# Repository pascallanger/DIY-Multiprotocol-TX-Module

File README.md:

# Multiprotocol TX Module

The **Multiprotocol Tx Module** (or **MULTI-Module**) is a 2.4GHz transmitter module which enables almost any transmitter to control many different receivers and models, including many popular helicopters, planes, quadcopters, and miniquads.

The main forum for protocol requests and questions is on [RCGroups.com](https://www.rcgroups.com/forums/showthread.php?2165676-DIY-Multiprotocol-TX-Module/page10000).

If you like this project and want to support further development please consider making a [donation](docs/Donations.md).  

<table cellspacing=0>
  <tr>
    <td align=center width=200><br><b>€5</b></td>
    <td align=center width=200><br><b>€10</b></td>
    <td align=center width=200><br><b>€15</b></td>
    <td align=center width=200><br><b>€25</b></td>
    <td align=center width=200><br><b>Other</b></td>
  </tr>
</table>

## Development status

Multiprotocol downloads: 

Current Multiprotocol code check status: . Download the latest **test** build [here](https://downloads.multi-module.org/latest-test/).

Current Multiprotocol boards check status: 

## Quicklinks
* [Download latest releases of the firmware](https://github.com/pascallanger/DIY-Multiprotocol-TX-Module/releases) and [instructions to upload .hex files](docs/Advanced_Manually_Setting_ATmega328_Fuses.md)
* [Forum on rcgroups](http://www.rcgroups.com/forums/showthread.php?t=2165676)
* [Available Protocols list](Protocols_Details.md)
* [The old documentation](docs/README-old.md)

## Outline of the documentation
1. Introduction (this page)
1. [Available protocols](Protocols_Details.md)
1. [Transmitters and serial/telemetry options](docs/Transmitters.md)
1. [Module Hardware options](docs/Hardware.md)
1. Compiling and programming the module
    * [Atmega328p Multiprotocol Module](docs/Compiling.md)
    * [STM32 Multiprotocol Module](docs/Compiling_STM32.md)
    * [OrangeRX Module](docs/Compiling_OrangeTx.md)
1. [Transmitter Setup](docs/Transmitters.md) 
    * [Channel Order](docs/Channel_Order.md)
1. [How to for popular models](docs/Models.md)
1. [Troubleshooting](docs/Troubleshooting.md)
2. [Advanced Topics (not for the fainthearted!)](docs/Advanced_Topics.md)

## Introduction
A functioning MULTI-Module consists of (see image below):  

1.  A host RC Tx

1. A Multiprotocol Transmitter Module (MULTI-Module) that connects to a host transmitter.  This module is typically comprised of
   * A microcontroller (currently ATMega328P or STM32) that interfaces with the Tx, controls the module functions and forwards the RC commands to the RF hardware
   * One or more (but at least one) RF modules that provide the capability to communicate with RC receivers.  To communicate with the receiver the RF module in the Tx must match with the RF module type in the receiver.  The four most common 2.4GHz RF chips on the market are supported TI CC2500, Nordic NRF24L01, Cypress CYRF6936, and the Amiccom A7105
   * MULTI-firmware loaded on to the microprocessor.  At a high level, this firmware performs a few different functions: 
     * It interfaces with signals from the host Tx and decodes these for transmission to the model, it manages the activation of the correct hardware RF module for each protocol
     * It implements the unique communication protocols for each receiver/model and manages the all-important binding process with a receiver/model
     * In the case of some protocols (for example DSMX and FrSky) it receives and decodes the telemetry information and makes this available to the radio.
1. The physical 2.4GHz antenna (or in some cases multiple antennas) for the modules

One of the most attractive features of the MULTI-module is the ability to send telemetry signals back to the transmitter. The MULTI-Module is fully telemetry capable for all protocols that support telemetry.  Your ability to use the telemetry information depends on  your radio hardware and firmware.

In constructing a functioning MULTI-Module there are important choices to be made and tradeoffs to be aware of.  The most important are:

## **Choice 1:** Which MULTI-Module hardware option 

There are currently four generic paths to get your hands on an MULTI-Module.  These are outlined in detail on the [hardware](docs/Hardware.md) page.  Here they are, in order of increasing difficulty:
  - **Ready-made MULTI-Module** - Available from Banggood which includes a 4-in-1 RF module and an antenna switcher
  - **DIY MULTI-Module** - Purchase one of the PCB options from [OSHPark](http://www.oshpark.com) and then solder on your own components and RF modules (the two options differ in the MCU used - either an ATmega328P or a STM32F1)
  - **OrangeRx MULTI-Module** You can turn the OrangeRx DSM2/X Tx module (available from HobbyKing) into a MULTI-Module to increase the number of supported protocols, add telemetry as an option and bind more successfully with problematic bind-and-fly models. 
  - **Scratchbuild a MULTI-Module** -  Build the module from scratch using perfboard base, an Arduino Pro Mini and discrete components.

The last option is where it all started and how the pioneers in this project made their boards.  However, due to the growing interest in “one module to rule them all” you now have options to purchase a ready-made board (with old firmware that you will need to upgrade).  

For more information on these options see the [hardware](docs/Hardware.md) page

## **Choice 2:** Which RF modules to include in the MULTI-Module

This depends on your specific needs.  However, recent the availability of the 4-in-1 RF modules from Banggood for less than $35 makes it easy to “have it all”.  Most manufacturers of RC systems (Spektrum, FrSky, FlySky) and toys (Syma, Hubsan, etc.) use one of these four RF chips to manage the RF link between the transmitter and the reciever/model.  Here is an incomplete list of the RF modules and some of the most popular toys that use them.  For the complete list see the [Protocol Details](Protocols_Details.md) page.

|Manufacturer|RF Chip|Example Protocols|
|---|---|---|
|Cyprus Semiconductor|CYRF6936|DSM/DSMX|
|||Walkera Devo|
|||J6Pro|
|Texas Instruments|CC2500|FrSky|
|||Futaba SFHSS|
|Amiccom|A7105|FlySky|
|||FlySky AFHDS2A|
|||Hubsan|
|Nordic Semiconductor|NRF24L01|HiSky|
|||Syma|
|||ASSAN|
|||and most other Chinese models|

For example, if you have no interest in binding your Tx to an model with and FrSky or Futaba SFHSS receiver you do not need to include the CC2500 RF module in your system.

## **Choice 3:** Which protocols to upload to the MULTI-Module

As the list of supported protocols grows even the STM32 ARM microcontroller cannot hold all of the protocols. You can select the protocols you need and complie your own firmware. Fortunately, the process of selecting and compiling is not too difficult and it is fully documented on the [Compiling and Programming](docs/Compiling.md) page. You can also download firmware from the [Multi-Module](https://downloads.multi-module.org) website. These firmware files have been split into two groups, surface "SFC" and air "AIR". You can check which protocols are included in each of these groups in the [Validate.h](Multiprotocol/Validate.h) source file.

In the case of the ATmega328, the memory required by all the possible protocols exceeds the 32KB flash limit considerably. This means that you will need to make a choice of which protocols you will compile into your firmware.

## **Choice 4:** Choosing the type of interface between the MULTI-Module and your radio (PPM or Serial)

The MULTI-Module supports industry standard PPM interface that works with all transmitters with either:  
 - a module bay or
 - a trainer port or
 - any PPM signal that can be accessed inside the Tx.

Most of the older FM radios support the PPM interface.

If you are the owner of a transmitter that supports the er9X/erSky9X or OpenTX firmwares (Frsky Taranis, Horus or the FlySky TH9X or the Turnigy 9X family) you have the additional option to use a serial protocol to communicate between your Tx and the MULTI-Module. (Owners of Walkera Devo transmitters should look at the [Deviation Tx](http://www.deviationtx.com) project for how to achieve the same end goal). This serial protocol does not require any hardware modifications, but will likely require updating the firmware on your radio. For those willing to do this, there are some nice advantages:
  - The model protocol selection, associated parameters, failsafe and binding is done from the Model Settings menu on the Tx
  - For telemetry capable transmitters, the telemetry integration is done seamlessly with the Tx firmware. (Note that FrSky TH9X/Turnigy 9X/R transmitters require a telemetry mod to be done before telemetry can work).  Click on the link corresponding to your Tx on the [Transmitters](docs/Transmitters.md) page for more details.

# How to get started?
1. Browse the [Protocols](Protocols_Details.md) page to see which protocols you would like on your module
1. Go to the [Hardware Options](docs/Hardware.md) page to decide which of the MULTI-Module hardware options appeals to you and which RF modules you plan to integrate
1. Once you have your module, you should review what jumper settings or modifications are required to the module to support serial communication and possibly telemetry
1. Go to [Compiling and Programming](docs/Compiling.md) page to download, compile and program your MULTI-Module
1. Finally, you should visit the setup page for your transmitter by clicking on the link corresponding to your Tx on the [Transmitters](docs/Transmitters.md) page to configure the last few settings before you can fly to your heart’s content!!!!!

# Troubleshooting
Visit the [Troubleshooting](docs/Troubleshooting.md) page.  Please bear in mind that the MULTI-Module is a complex system of hardware and software and it may take some patience to get it up and running.  Also remember that the developers of the system are actual users of the system.  This means that at any moment in time the system is working perfectly for them.  A corollary to this is that if you are struggling there are likely two scenarios.  First, that the problem is with your hardware or with your configuration, second, and much more unlikely but not impossible scenario, is that you are struggling with a new undiscovered bug.  (The author of this documentation speaks from experience ;-)   Please check the RC Groups forum and search for keywords relating to your problem before posting a reply.  When you do post a reply please so humbly and respectfully – you will find many helpful people there.  In your reply please include as much relevant information as possible and attach compilation output and ```_Config.h``` files as text attachments to keep the forum clean.
# A final word
A very big thanks to all the people who have shared their time so graciously to create this great project.  If you come across them on RC Groups, please be kind and show appreciation.  In no particular order:
* Pascal Langer (rcgroups: hpnuts)
* Ben Lye (rcgroups: benzo99)
* Midelic (rcgroups: midelic)
* Mike Blandford (rcgroups: Mike Blandford)
* schwabe - from OpenTX 
* PhracturedBlue – from [Deviation TX project](http://www.deviationtx.com)
* goebish – from [Deviation TX project](http://www.deviationtx.com)
* victzh – from [Deviation TX project](http://www.deviationtx.com)
* hexfet – from [Deviation TX project](http://www.deviationtx.com)

Your help would be greatly appreciated.  If protocol reverse-engineering and dev is not your thing then any help with testing and contributing to the documentation would be amazing.  Given the number of different Tx/module hardware/RF module/protocol/model combinations the process of testing and documenting is a major bottleneck for the developers.  Anything you can do to help will free them up to do even greater things. 

If you like this project and want to support further development please consider making a [donation](docs/Donations.md).

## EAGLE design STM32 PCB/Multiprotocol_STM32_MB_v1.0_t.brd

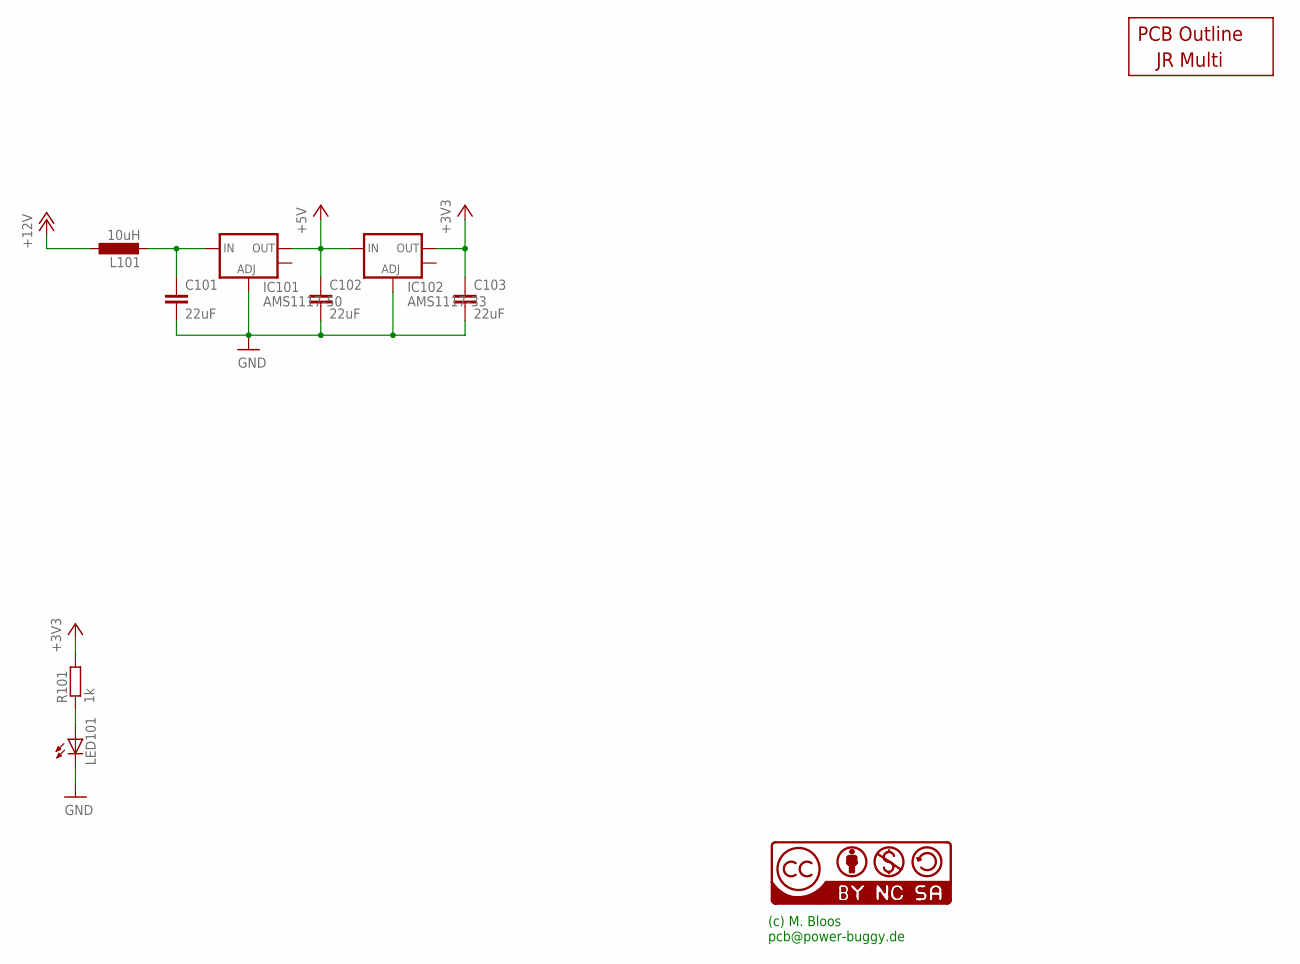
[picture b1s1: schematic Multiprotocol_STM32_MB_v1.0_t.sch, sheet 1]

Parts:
C101, C102, C103: 22uF; C1210K
IC101: AMS1117-50; SOT223
IC102: AMS1117-33; SOT223
L101: 10uH; L1812
LED101: LED3MM
NIX101: CC-NC-BCNIX; CC-NC-B_NIX
OUTLINE101: JR_MULTI
R101: 1k; R0805

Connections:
+3V3: C103.1, IC102.2 (OUT), R101.2; also elsewhere on the board
+5V: C102.1, IC101.2 (OUT), IC102.3 (IN); also elsewhere on the board
+12V: L101.1; also elsewhere on the board
GND: C101.2, C102.2, C103.2, IC101.1 (ADJ), IC102.1 (ADJ), LED101.K (C); also elsewhere on the board
unnamed: C101.1, IC101.3 (IN), L101.2
unnamed: LED101.A, R101.1

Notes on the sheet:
(c) M. Bloos pcb@power-buggy.de

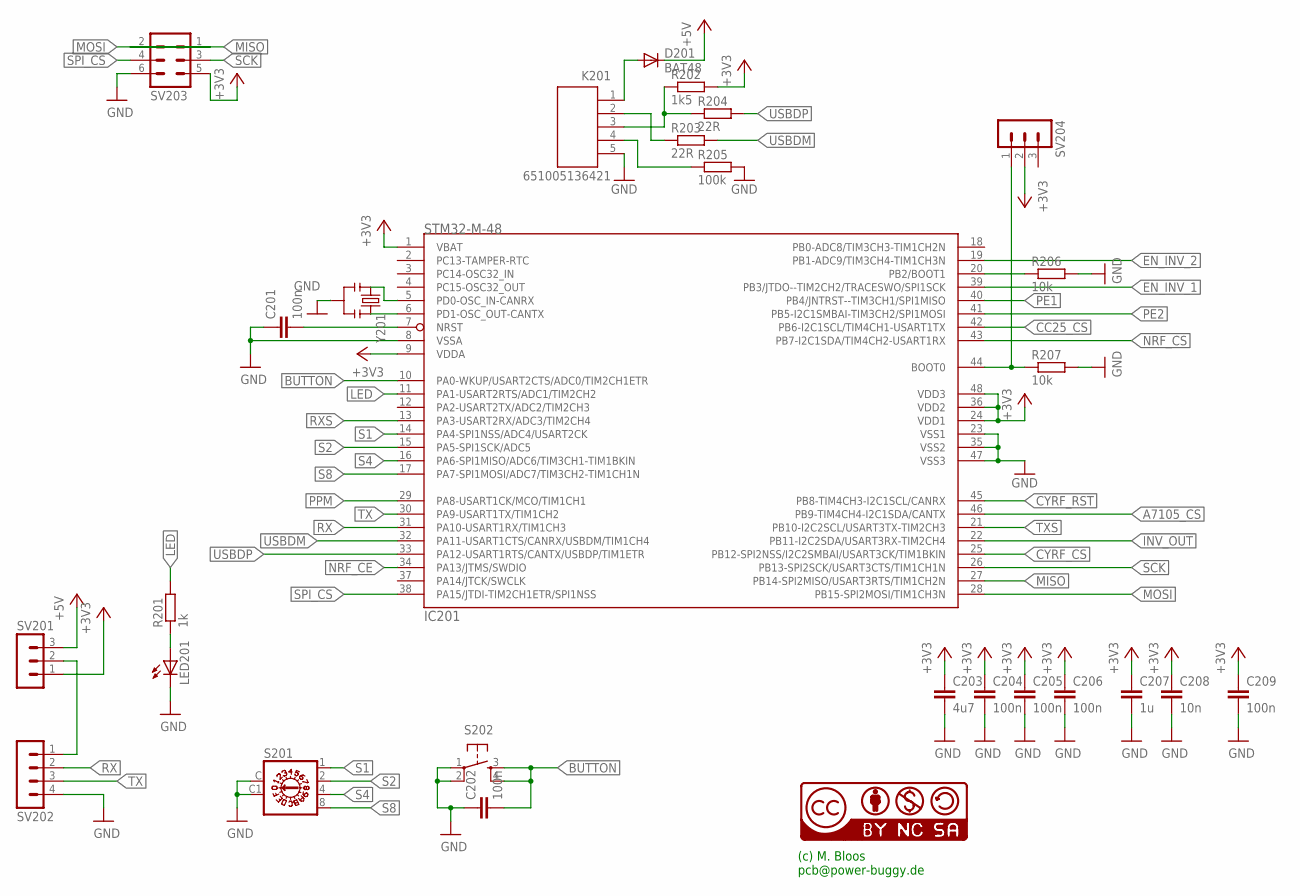
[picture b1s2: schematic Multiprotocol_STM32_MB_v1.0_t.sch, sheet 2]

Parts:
C201, C202, C204, C205, C206, C209: 100n; C0805
C203: 4u7; C0805
C207: 1u; C0805
C208: 10n; C0805
D201: BAT48; MINIMELF
IC201: STM32-M-48; LQFP48
K201: 651005136421
LED201: LED3MM
NIX201: CC-NC-BCNIX; CC-NC-B_NIX
R201: 1k; R0805
R202: 1k5; R0805
R203, R204: 22R; R0805
R205: 100k; R0805
R206, R207: 10k; R0805
S201: A1353HEX
S202: TAC_SWITCHPTH; TACTILE-PTH
SV201, SV204: MA03-1
SV202: MA04-1
SV203: MA03-2
Y201: CSTCE8M00G52-R0; RESONATOR-SMD

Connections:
+3V3: C203.1, C204.1, C205.1, C206.1, C207.1, C208.1, C209.1, IC201.1 (VBAT), IC201.9 (VDDA), IC201.24 (VDD1), IC201.36 (VDD2), IC201.48 (VDD3), R202.2, SV201.1, SV203.5, SV204.2; also elsewhere on the board
+5V: D201.C, SV201.3; also elsewhere on the board
A7105_CS: IC201.46 (PB9-TIM4CH4-I2C1SDA/CANTX); also elsewhere on the board
BUTTON: C202.2, IC201.10 (PA0-WKUP/USART2CTS/ADC0/TIM2CH1ETR), S202.3, S202.4
CC25_CS: IC201.42 (PB6-I2C1SCL/TIM4CH1-USART1TX); also elsewhere on the board
CYRF_CS: IC201.25 (PB12-SPI2NSS/I2C2SMBAI/USART3CK/TIM1BKIN); also elsewhere on the board
CYRF_RST: IC201.45 (PB8-TIM4CH3-I2C1SCL/CANRX); also elsewhere on the board
EN_INV_1: IC201.39 (PB3/JTDO--TIM2CH2/TRACESWO/SPI1SCK); also elsewhere on the board
EN_INV_2: IC201.19 (PB1-ADC9/TIM3CH4-TIM1CH3N); also elsewhere on the board
GND: C201.1, C202.1, C203.2, C204.2, C205.2, C206.2, C207.2, C208.2, C209.2, IC201.8 (VSSA), IC201.23 (VSS1), IC201.35 (VSS2), IC201.47 (VSS3), K201.5, LED201.K (C), R205.2, R206.2, R207.2, S201.C, S201.C1 (NC), S202.1, S202.2, SV202.4, SV203.6, Y201.2; also elsewhere on the board
INV_OUT: IC201.22 (PB11-I2C2SDA/USART3RX-TIM2CH4); also elsewhere on the board
LED: IC201.11 (PA1-USART2RTS/ADC1/TIM2CH2), R201.2
MISO: IC201.27 (PB14-SPI2MISO/USART3RTS/TIM1CH2N), SV203.2; also elsewhere on the board
MOSI: IC201.28 (PB15-SPI2MOSI/TIM1CH3N), SV203.1; also elsewhere on the board
unnamed: IC201.5 (PD0-OSC_IN-CANRX), Y201.1
unnamed: IC201.6 (PD1-OSC_OUT-CANTX), Y201.3
unnamed: SV201.2, SV202.1
unnamed: K201.4, R205.1
unnamed: LED201.A, R201.1
unnamed: C201.2, IC201.7 (NRST)
unnamed: K201.3, R202.1, R204.1
unnamed: D201.A, K201.1
unnamed: K201.2, R203.1
unnamed: IC201.44 (BOOT0), R207.1, SV204.1
unnamed: IC201.20 (PB2/BOOT1), R206.1
NRF_CE: IC201.34 (PA13/JTMS/SWDIO); also elsewhere on the board
NRF_CS: IC201.43 (PB7-I2C1SDA/TIM4CH2-USART1RX); also elsewhere on the board
PE1: IC201.40 (PB4/JNTRST--TIM3CH1/SPI1MISO); also elsewhere on the board
PE2: IC201.41 (PB5-I2C1SMBAI-TIM3CH2/SPI1MOSI); also elsewhere on the board
PPM: IC201.29 (PA8-USART1CK/MCO/TIM1CH1); also elsewhere on the board
RX: IC201.31 (PA10-USART1RX/TIM1CH3), SV202.2
RXS: IC201.13 (PA3-USART2RX/ADC3/TIM2CH4); also elsewhere on the board
S1: IC201.14 (PA4-SPI1NSS/ADC4/USART2CK), S201.1
S2: IC201.15 (PA5-SPI1SCK/ADC5), S201.2
S4: IC201.16 (PA6-SPI1MISO/ADC6/TIM3CH1-TIM1BKIN), S201.4
S8: IC201.17 (PA7-SPI1MOSI/ADC7/TIM3CH2-TIM1CH1N), S201.8
SCK: IC201.26 (PB13-SPI2SCK/USART3CTS/TIM1CH1N), SV203.3; also elsewhere on the board
SPI_CS: IC201.38 (PA15/JTDI-TIM2CH1ETR/SPI1NSS), SV203.4
TX: IC201.30 (PA9-USART1TX/TIM1CH2), SV202.3
TXS: IC201.21 (PB10-I2C2SCL/USART3TX-TIM2CH3); also elsewhere on the board
USBDM: IC201.32 (PA11-USART1CTS/CANRX/USBDM/TIM1CH4), R203.2
USBDP: IC201.33 (PA12-USART1RTS/CANTX/USBDP/TIM1ETR), R204.2

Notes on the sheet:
(c) M. Bloos pcb@power-buggy.de

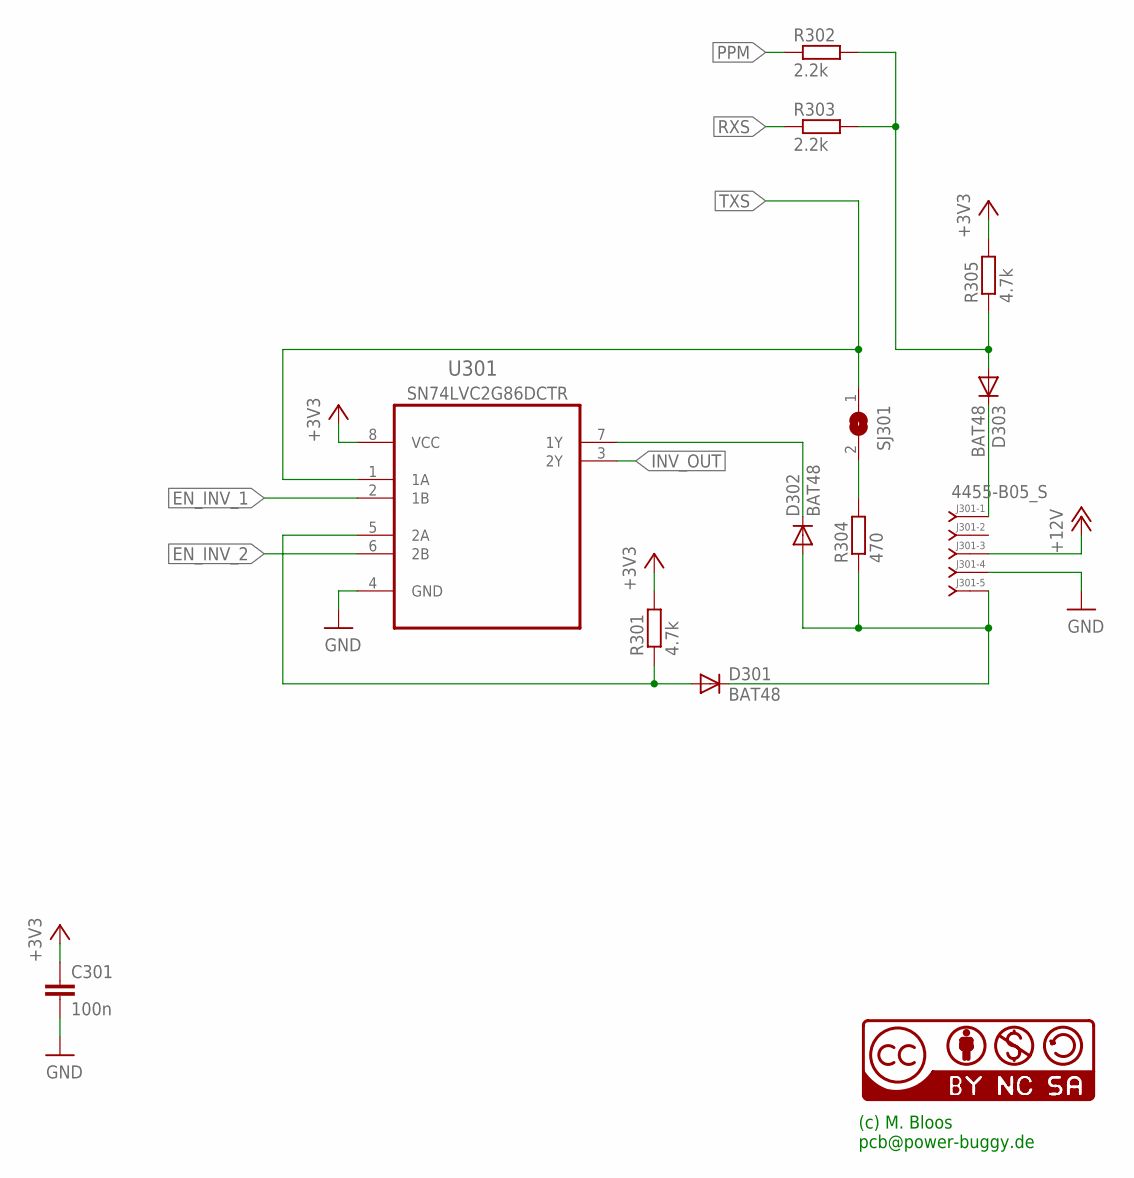
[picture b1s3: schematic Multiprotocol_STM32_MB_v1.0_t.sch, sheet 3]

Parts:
C301: 100n; C0805
D301, D302, D303: BAT48; MINIMELF
J301: 4455-B05_S; 4455-B05
NIX301: CC-NC-BCNIX; CC-NC-B_NIX
R301, R305: 4.7k; R0805
R302, R303: 2.2k; R0805
R304: 470; R0805
SJ301: SJ
U301: SN74LVC2G00DCTR; SOP65P400X130-8N

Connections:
+3V3: C301.1, R301.2, R305.2, U301.8 (VCC); also elsewhere on the board
+12V: J301.3; also elsewhere on the board
EN_INV_1: U301.2 (1B); also elsewhere on the board
EN_INV_2: U301.6 (2B); also elsewhere on the board
GND: C301.2, J301.4, U301.4 (GND); also elsewhere on the board
INV_OUT: U301.3 (2Y); also elsewhere on the board
unnamed: D302.C, U301.7 (1Y)
unnamed: R304.2, SJ301.2
unnamed: D301.A, R301.1, U301.5 (2A)
unnamed: D301.C, D302.A, J301.5, R304.1
unnamed: D303.A, R302.2, R303.2, R305.1
unnamed: D303.C, J301.1
PPM: R302.1; also elsewhere on the board
RXS: R303.1; also elsewhere on the board
TXS: SJ301.1, U301.1 (1A); also elsewhere on the board

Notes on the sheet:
SN74LVC2G86DCTR
(c) M. Bloos pcb@power-buggy.de

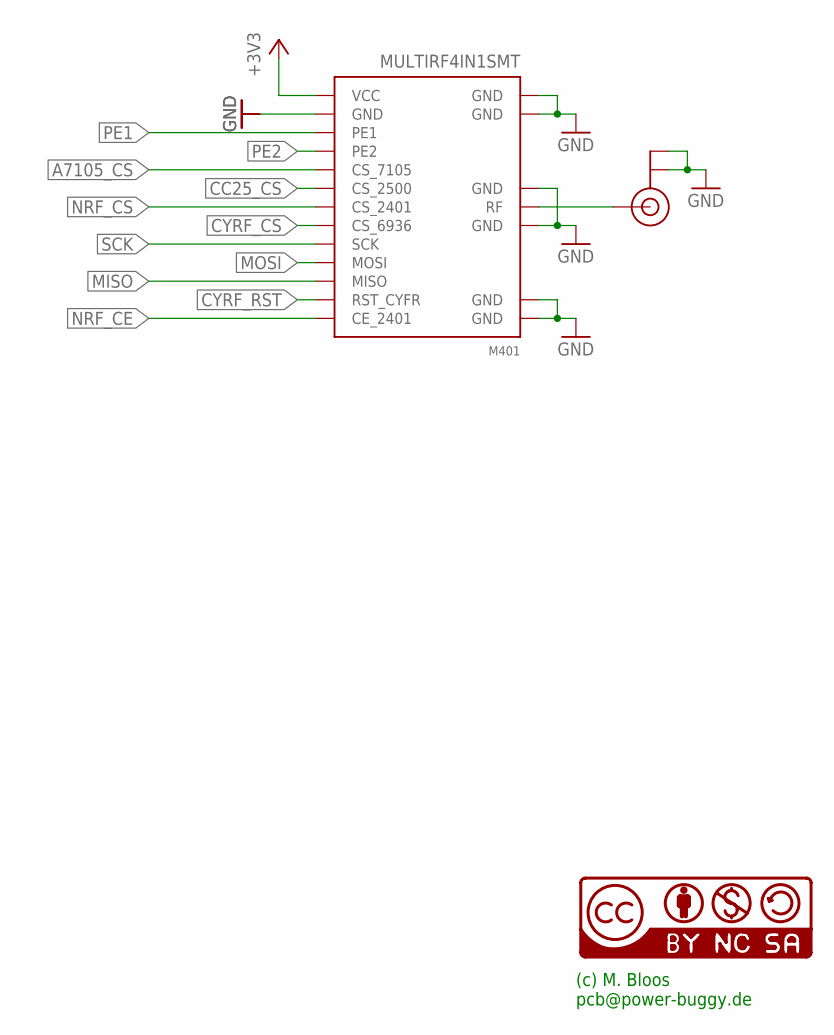
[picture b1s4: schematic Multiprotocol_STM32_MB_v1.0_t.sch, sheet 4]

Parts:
CON401: U.FL
M401: MULTIRF4IN1SMT; MULTIRF4IN1-SMT
NIX401: CC-NC-BCNIX; CC-NC-B_NIX

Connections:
+3V3: M401.VCC; also elsewhere on the board
A7105_CS: M401.CS_7105; also elsewhere on the board
CC25_CS: M401.CS_2500; also elsewhere on the board
CYRF_CS: M401.CS_6936; also elsewhere on the board
CYRF_RST: M401.RST_CYFR; also elsewhere on the board
GND: CON401.P$1 (GND), CON401.P$2 (GND), M401.GND, M401.GND@1 (GND), M401.GND@2 (GND), M401.GND@3 (GND), M401.GND@4 (GND), M401.GND@5 (GND), M401.GND@6 (GND); also elsewhere on the board
MISO: M401.MISO; also elsewhere on the board
MOSI: M401.MOSI; also elsewhere on the board
unnamed: CON401.P$3 (SIGNAL), M401.RF
NRF_CE: M401.CE_2401; also elsewhere on the board
NRF_CS: M401.CS_2401; also elsewhere on the board
PE1: M401.PE1; also elsewhere on the board
PE2: M401.PE2; also elsewhere on the board
SCK: M401.SCK; also elsewhere on the board

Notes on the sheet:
(c) M. Bloos pcb@power-buggy.de

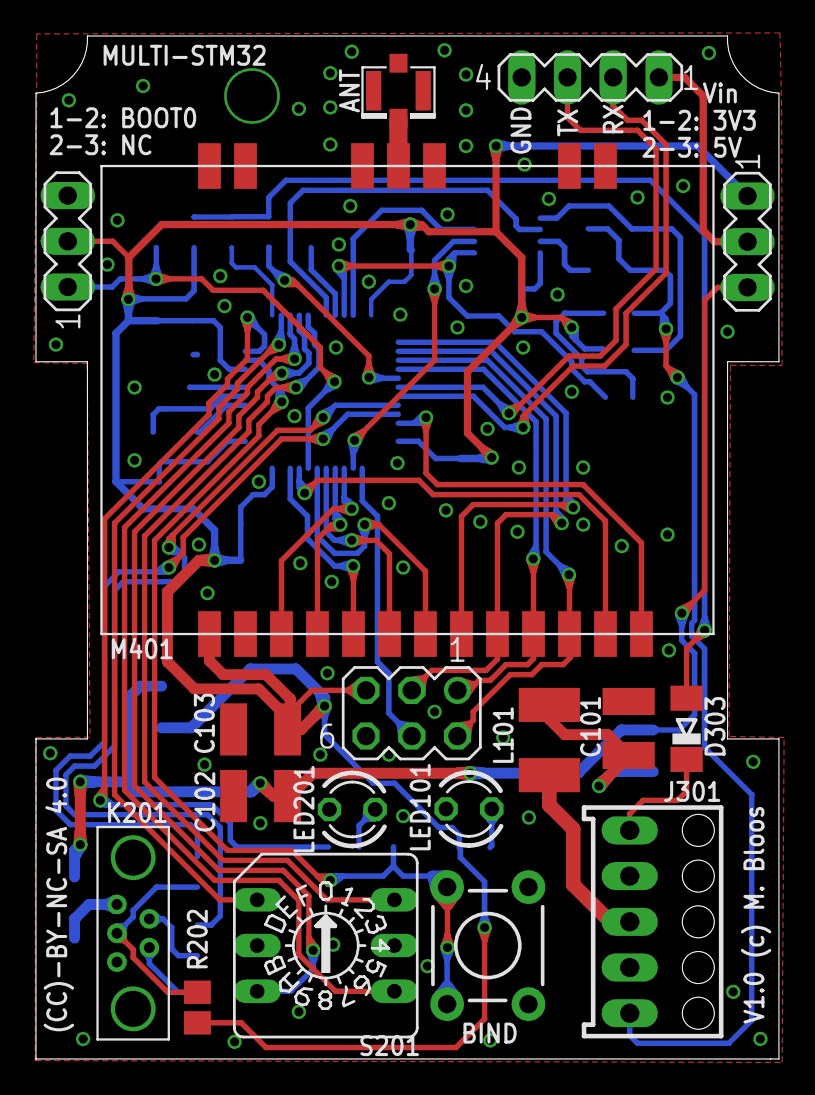
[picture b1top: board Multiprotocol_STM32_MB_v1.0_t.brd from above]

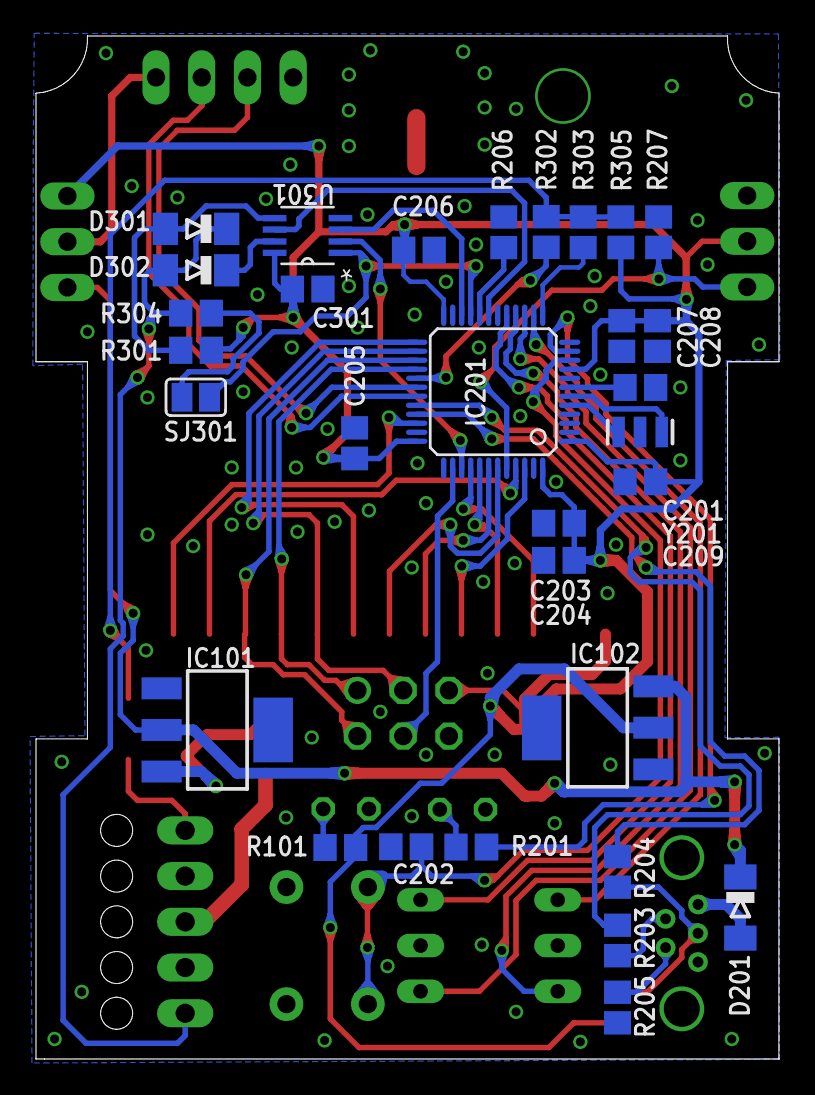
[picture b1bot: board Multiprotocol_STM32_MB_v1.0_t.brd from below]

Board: 2 copper layers, 41.3 x 56.8 mm, 54 parts (31 on the bottom side), 52 nets.

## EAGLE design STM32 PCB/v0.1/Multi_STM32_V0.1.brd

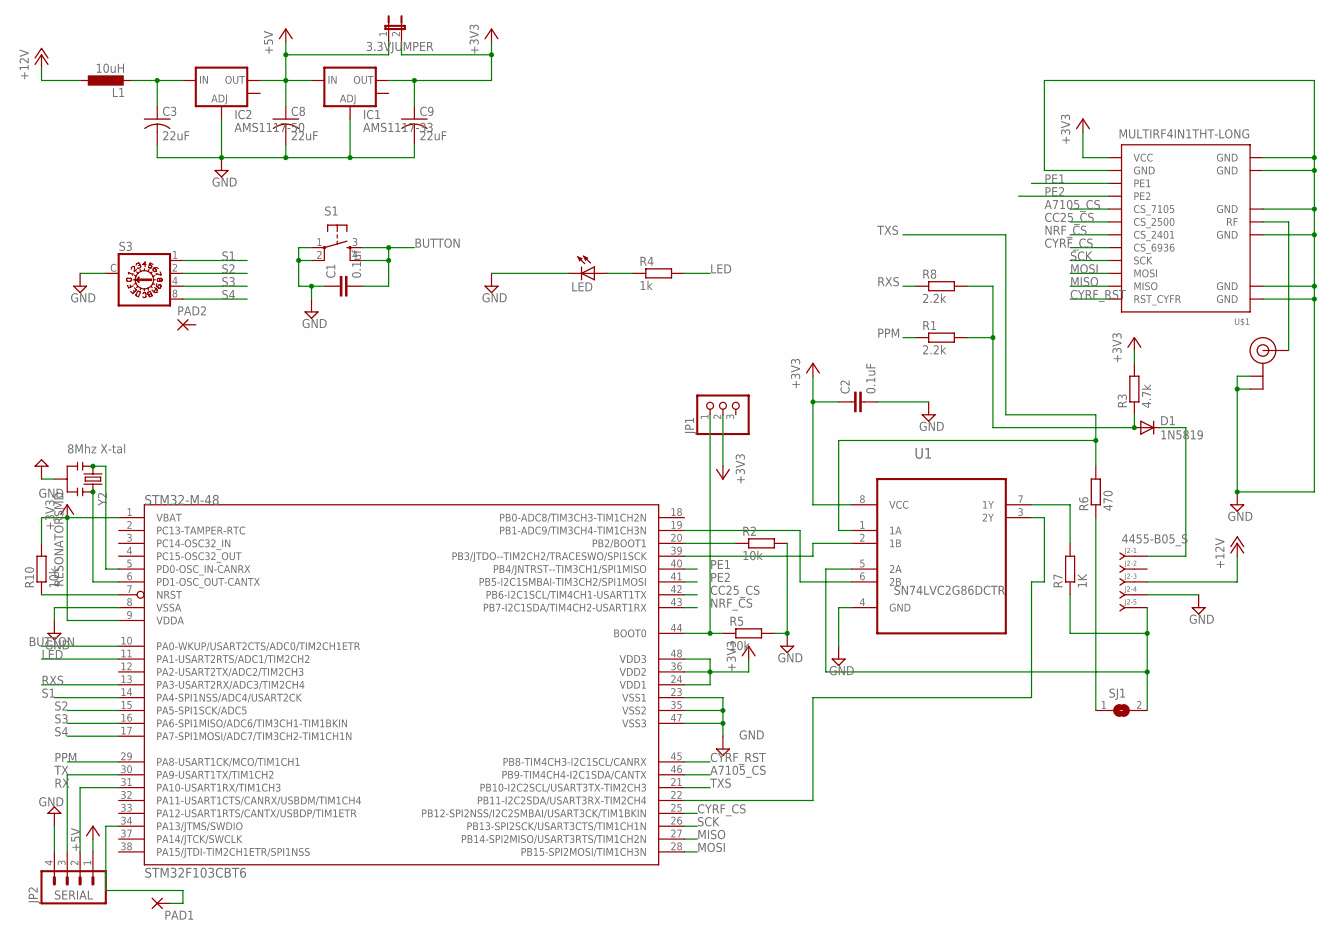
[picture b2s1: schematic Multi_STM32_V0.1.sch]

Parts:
3.3VJUMPER: JUMPER-2PTH; 1X02
C1: 0.1uf; C0805
C2: 0.1uF; C0805
C3, C8, C9: 22uF; C1206
D1: 1N5819; SMA-DIODE_ALT
IC1: AMS1117-33; SOT223
IC2: AMS1117-50; SOT223
J2: 4455-B05_S; 4455-B05
JP1: PINHD-1X3; 1X03
JP2: SERIAL; 1X04
L1: 10uH; L1812
LED: LED3MM
PAD1: SMD2; SMD1,27-2,54
PAD2: 1,6/0,8
R1, R8: 2.2k; R0805
R2, R5, R10: 10k; R0805
R3: 4.7k; R0805
R4: 1k; R0805
R6: 470; R0805
R7: 1K; R0805
S1: TAC_SWITCHPTH; TACTILE-PTH
S3: A1353HEX
SJ1: SJ
STM32F103CBT6: STM32-M-48; LQFP48
U1: SN74LVC2G00DCTR; SOP65P400X130-8N
U$1: MULTIRF4IN1THT-LONG; MULTIRF4IN1-THT-LONG
U$2: U.FL
Y2: RESONATORSMD; RESONATOR-SMD

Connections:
+3V3: 3.3VJUMPER.2, C2.1, C9.1, IC1.2 (OUT), JP1.2, R3.2, R10.2, STM32F103CBT6.1 (VBAT), STM32F103CBT6.9 (VDDA), STM32F103CBT6.24 (VDD1), STM32F103CBT6.36 (VDD2), STM32F103CBT6.48 (VDD3), U1.8 (VCC), U$1.VCC
+5V: 3.3VJUMPER.1, C8.1, IC1.3 (IN), IC2.2 (OUT), JP2.1
+12V: J2.3, L1.1
A7105_CS: STM32F103CBT6.46 (PB9-TIM4CH4-I2C1SDA/CANTX), U$1.CS_7105
BUTTON: C1.2, S1.3, S1.4, STM32F103CBT6.10 (PA0-WKUP/USART2CTS/ADC0/TIM2CH1ETR)
CC25_CS: STM32F103CBT6.42 (PB6-I2C1SCL/TIM4CH1-USART1TX), U$1.CS_2500
CYRF_CS: STM32F103CBT6.25 (PB12-SPI2NSS/I2C2SMBAI/USART3CK/TIM1BKIN), U$1.CS_6936
CYRF_RST: STM32F103CBT6.45 (PB8-TIM4CH3-I2C1SCL/CANRX), U$1.RST_CYFR
GND: C1.1, C2.2, C3.2, C8.2, C9.2, IC1.1 (ADJ), IC2.1 (ADJ), J2.4, JP2.4, LED.K (C), R2.2, R5.2, S1.1, S1.2, S3.C, STM32F103CBT6.8 (VSSA), STM32F103CBT6.23 (VSS1), STM32F103CBT6.35 (VSS2), STM32F103CBT6.47 (VSS3), U1.4 (GND), U$1.GND, U$1.GND@1 (GND), U$1.GND@2 (GND), U$1.GND@3 (GND), U$1.GND@4 (GND), U$1.GND@5 (GND), U$1.GND@6 (GND), U$2.P$1 (GND), U$2.P$2 (GND), Y2.2
LED: R4.2, STM32F103CBT6.11 (PA1-USART2RTS/ADC1/TIM2CH2)
MISO: STM32F103CBT6.27 (PB14-SPI2MISO/USART3RTS/TIM1CH2N), U$1.MISO
MOSI: STM32F103CBT6.28 (PB15-SPI2MOSI/TIM1CH3N), U$1.MOSI
unnamed: R6.1, SJ1.1
unnamed: STM32F103CBT6.5 (PD0-OSC_IN-CANRX), Y2.1
unnamed: STM32F103CBT6.6 (PD1-OSC_OUT-CANTX), Y2.3
unnamed: C3.1, IC2.3 (IN), L1.2
unnamed: STM32F103CBT6.39 (PB3/JTDO--TIM2CH2/TRACESWO/SPI1SCK), U1.2 (1B)
unnamed: STM32F103CBT6.22 (PB11-I2C2SDA/USART3RX-TIM2CH4), U1.3 (2Y)
unnamed: PAD1.1, STM32F103CBT6.34 (PA13/JTMS/SWDIO)
unnamed: R7.2, U1.7 (1Y)
unnamed: J2.5, R7.1, SJ1.2, U1.5 (2A)
unnamed: LED.A, R4.1
unnamed: R10.1, STM32F103CBT6.7 (NRST)
unnamed: STM32F103CBT6.19 (PB1-ADC9/TIM3CH4-TIM1CH3N), U1.6 (2B)
unnamed: D1.A, R1.2, R3.1, R8.2
unnamed: U$1.RF, U$2.P$3 (SIGNAL)
unnamed: D1.C, J2.1
unnamed: JP1.1, R5.1, STM32F103CBT6.44 (BOOT0)
unnamed: R2.1, STM32F103CBT6.20 (PB2/BOOT1)
NRF_CS: STM32F103CBT6.43 (PB7-I2C1SDA/TIM4CH2-USART1RX), U$1.CS_2401
PE1: STM32F103CBT6.40 (PB4/JNTRST--TIM3CH1/SPI1MISO), U$1.PE1
PE2: STM32F103CBT6.41 (PB5-I2C1SMBAI-TIM3CH2/SPI1MOSI), U$1.PE2
PPM: R1.1, STM32F103CBT6.29 (PA8-USART1CK/MCO/TIM1CH1)
RX: JP2.2, STM32F103CBT6.31 (PA10-USART1RX/TIM1CH3)
RXS: R8.1, STM32F103CBT6.13 (PA3-USART2RX/ADC3/TIM2CH4)
S1: S3.1, STM32F103CBT6.14 (PA4-SPI1NSS/ADC4/USART2CK)
S2: S3.2, STM32F103CBT6.15 (PA5-SPI1SCK/ADC5)
S3: S3.4, STM32F103CBT6.16 (PA6-SPI1MISO/ADC6/TIM3CH1-TIM1BKIN)
S4: S3.8, STM32F103CBT6.17 (PA7-SPI1MOSI/ADC7/TIM3CH2-TIM1CH1N)
SCK: STM32F103CBT6.26 (PB13-SPI2SCK/USART3CTS/TIM1CH1N), U$1.SCK
TX: JP2.3, STM32F103CBT6.30 (PA9-USART1TX/TIM1CH2)
TXS: R6.2, STM32F103CBT6.21 (PB10-I2C2SCL/USART3TX-TIM2CH3), U1.1 (1A)

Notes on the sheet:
SN74LVC2G86DCTR
8Mhz X-tal

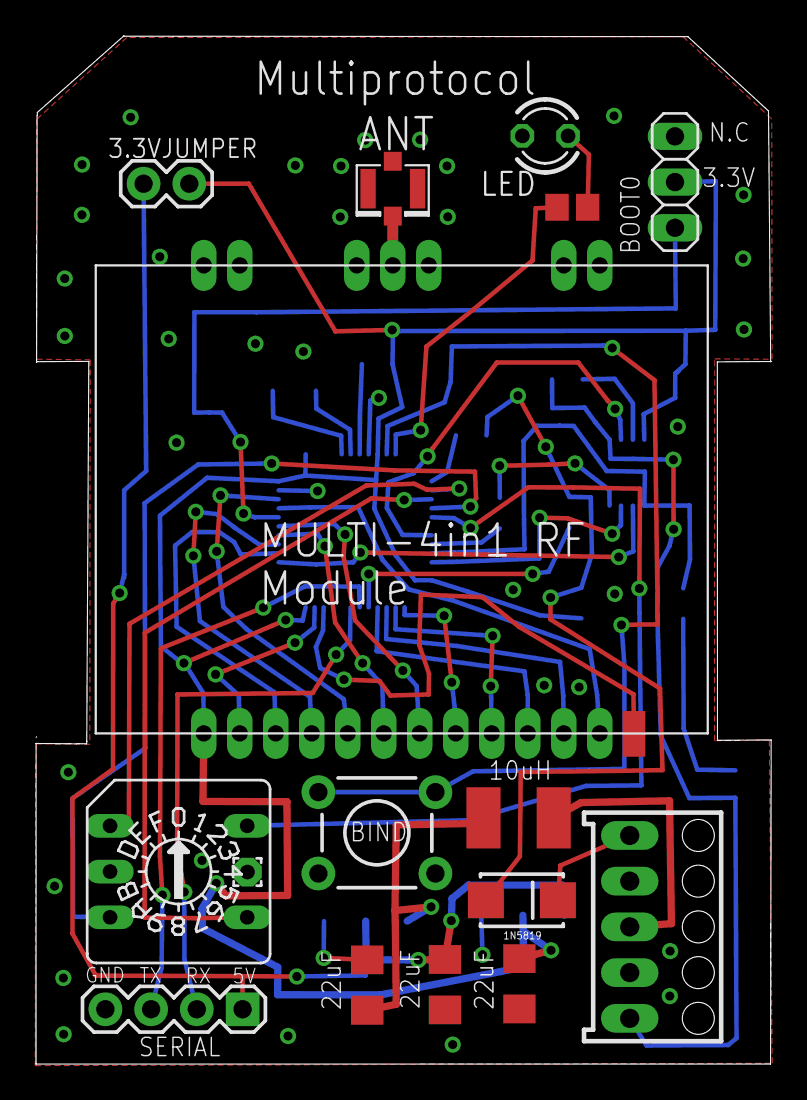
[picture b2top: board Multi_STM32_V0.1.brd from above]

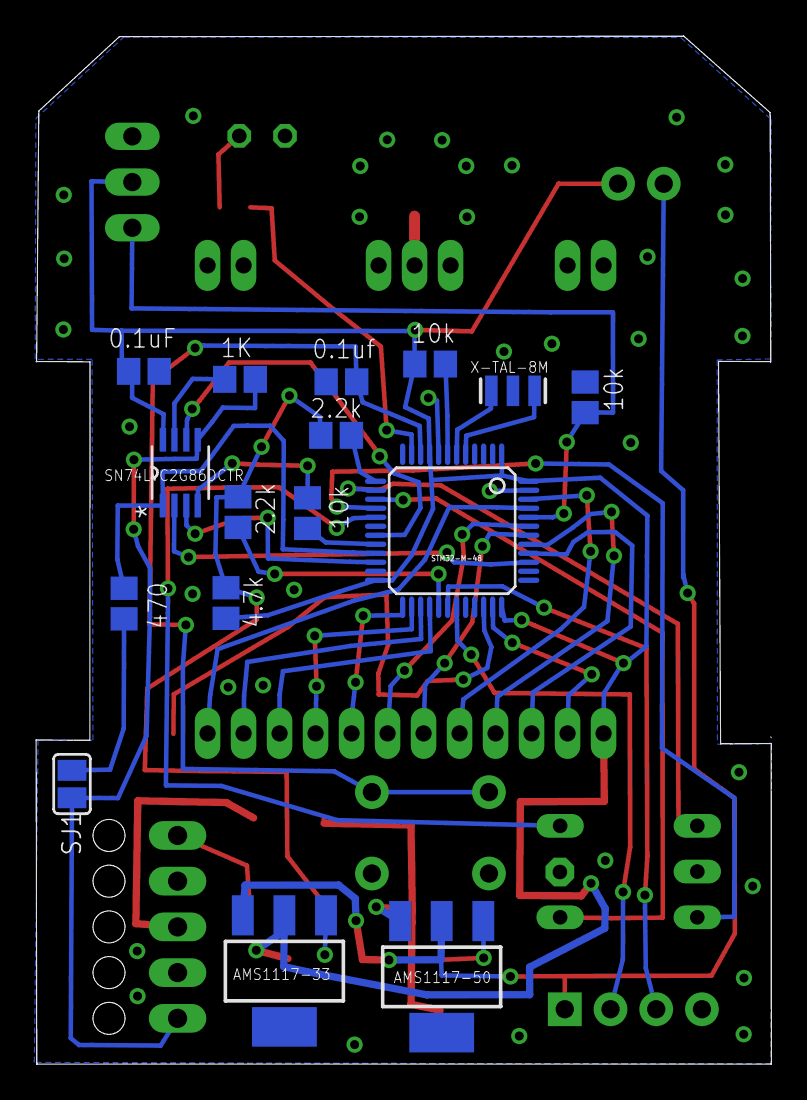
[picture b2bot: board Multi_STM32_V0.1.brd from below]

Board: 2 copper layers, 40.9 x 57.1 mm, 33 parts (16 on the bottom side), 42 nets.

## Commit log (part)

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2024-02-22 Improve artifact merge
2024-02-22 Tweak CI job name
2024-02-22 Bump action versions
2024-02-22 Remove CFlie from DIY 5-in-1 AIR
2024-02-22 T18 air, surface, and LBT builds
2024-02-22 Add T-Lite 5-in-1 LBT
2024-02-22 Fix merge
2024-02-23 CI job restructure
2024-02-23 Remove DSMR when MULTI_AIR
2024-02-23 Remove Radiolink/RC4G when MULTI_AIR
2024-02-23 Automated build process updates (#950)
    * 4-in-1 air and surface builds
    * Disable serial and PPM-only builds for STM32 x-in-1
    * More air and surface builds
    * Fix 5-in-1 tests
    * T18 air, surface, and LBT builds
    * Remove CFlie from DIY 5-in-1 AIR
2024-02-23 Bumping revision
2024-02-23 Rename Traxxas/6519 to Traxxas/TQ
2024-02-23 New protocol EazyRC
2024-02-23 EazyRC.1
2024-02-23 EazyRC.2
2024-02-26 Radiolink/RC4G: IDs and RFs
2024-02-28 EazyRC multi IDs/RFs
2024-03-14 Update Protocols_Details.md (#955)
2024-03-14 REALACC multi IDs
2024-03-17 Docs update
2024-03-18 DSM/DSM2SFC new subprotocol
2024-03-19 DSM2SFC timing update
2024-03-21 SGF22: Fix none working IDs
2024-03-22 New protocol Kyosho3/ASF
    Only 1 ID and 1 frequency for now
2024-03-22 Kyosho3: increase bind time to 2.5s
2024-03-23 ASF: try 1
2024-03-25 CYRF6936: Findbestchannels flag addition
2024-03-25 ASF try 2
2024-03-26 ASF try 3
2024-03-26 DSM2_SFC try 1
    Servo refresh rate -> frame rate 16.5/11ms
2024-03-26 DSM2_SFC try 2
2024-03-26 DSM2_SFC try 3
2024-03-29 ASF try 4
2024-03-29 SGF22: new flag
2024-04-02 REALACC: IDs
    Any ID
2024-04-02 Realacc doc update
2024-04-04 Traxxas TQ 6 channels
2024-04-12 SLT try 1
2024-04-12 SLT try 1a
2024-04-13 SLT try 1b
2024-04-14 SLT try 1c
2024-04-14 SLT try 1d
2024-04-15 SLT new sub_protocol V1_4CH
2024-04-18 SLT try 1e
2024-04-26 Traxxas TQ 1st gen: try 1
2024-04-27 Traxxas TQ 1st gen: try 2
2024-05-02 Traxxas TQ 1st gen: try 4
2024-05-04 J6Pro update
2024-05-04 Traxxas TQ 1st gen: try 5
2024-05-17 FX/Q560 new sub protocol
2024-05-21 Update FX/Q560 doc
2024-06-07 New protocol XK2 for the XK A160S
2024-06-14 Disable SCANNER ...
2024-06-14 Disable SCANNER ... (#989)
2024-07-11 E129/C185 new debug flag
2024-07-12 XK2: 1 TX ID but multiple RX IDs?
2024-07-18 chore(ci): bump setup-arduino-ci version to remove nodejs warning
    Gets rid of the numerous "The following actions
    uses Node.js version which is deprecated and will
    be forced to run on node20" warnings
2024-07-18 chore: bump arduino-cli ver
2024-07-18 chore(ci): bump setup-arduino-ci version to remove nodejs warning (#995)
    * chore(ci): bump setup-arduino-ci version to remove nodejs warning
    Gets rid of the numerous "The following actions
    uses Node.js version which is deprecated and will
    be forced to run on node20" warnings
    * chore: bump arduino-cli ver
2024-07-24 Revert main.yml to use the old version of arduino_cli
2024-09-01 add PTF22S - Update SGF22_nrf24l01.ino
2024-09-01 add PTF22S - Update Multi_Protos.ino
2024-09-01 add PTF22S - Update Multiprotocol.h
2024-09-01 add PTF22S - Update _Config.h
2024-09-02 SGF22: new F22S sub protocol
2024-09-26 Update _Config.h
    add sub protocol "J20" to "SGF22" protocol
2024-09-26 Update Multi.txt
    add sub protocol "J20" to "SGF22" protocol
2024-09-26 Update Multi_Protos.ino
    add sub protocol "J20" to "SGF22" protocol
2024-09-26 Update Multiprotocol.h
    add sub protocol "J20" to "SGF22" protocol
2024-09-26 Update SGF22_nrf24l01.ino
    add sub protocol "J20" to "SGF22" protocol
2024-09-26 Update _Config.h (#1019)
    add sub protocol "J20" to "SGF22" protocol
2024-09-26 Update Multi.txt (#1020)
    add sub protocol "J20" to "SGF22" protocol
2024-09-26 Update Multi_Protos.ino (#1021)
    add sub protocol "J20" to "SGF22" protocol
2024-09-26 Update Multiprotocol.h (#1022)
    add sub protocol "J20" to "SGF22" protocol
2024-09-26 Update SGF22_nrf24l01.ino (#1023)
    add sub protocol "J20" to "SGF22" protocol
2024-09-28 Update MT99xx_ccnrf.ino
    add QF009 Su35 support to MT99XX protocol / H7 sub protocol
2024-10-03 Update SGF22_nrf24l01.ino
    Add "FixHeight(Altitude hold)" flag to J20
2024-10-03 Update Multi.txt
    Add SU35 protocol
2024-10-03 Update Multi_Protos.ino
    Add SU35 protocol
2024-10-03 Update _Config.h
    Add SU35 protocol
2024-10-03 Update Multiprotocol.h
    Add SU35 protocol
2024-10-03 Update MT99xx_ccnrf.ino
    Add SU35 protocol
    Pls add in the web page
    https://github.com/pascallanger/DIY-Multiprotocol-TX-Module/blob/master/Protocols_Details.md#MT99XX2---92
    Sub_protocol SU35
    Model: QF009 Su35, CH5 - mode -100% = 6G 100% = 3D, CH6 - LED, CH7 - LED Flash, CH8 - Invert, CH9 - Rate
2024-10-05 Update readme and protocol detals with surface/air info
2025-01-07 V761 Beeper feature on CH10
2025-01-13 YuXiang E190 protocol
    Only 1 ID, bind might not work...
2025-01-15 Yuxiang TX2
2025-01-16 Yuxiang remove CH8
2025-01-17 Yuxiang bind ok
2025-01-18 Yuxiang telemetry
    Offset=7, Ratio=3.5
2025-01-19 Added sub-protocol RF_SIM to the SLT protocol
2025-01-19 fixed typo
2025-01-19 Add RF_SIM sub-protocol to SLT-protocol (#1061)
    * Added sub-protocol RF_SIM to the SLT protocol
    * fixed typo
    ---------
2025-01-19 Update readme and protocol detals with surface/air info (#1034)
    * Update readme and protocol detals with surface/air info
    * Update Protocols_Details.md
    * Update README.md
    ---------
2025-01-19 Traxxas TQ2&TQ1
2025-01-19 Add MT99xx2/SU35 protocol (#1033)
    * Update Multi.txt
    * Update Multi_Protos.ino
    * Update _Config.h
    * Update Multiprotocol.h
    * Update MT99xx_ccnrf.ino
2025-01-19 MT99X2/SU35
2025-01-20 XK2 2nd ID
2025-01-20 XK2 multi IDs
2025-01-21 XK2 details
2025-01-23 QIDI560 new light flag?
2025-01-25 SGF22 Flags trial
2025-01-25 SGF22 FX922 flags
2025-01-27 New car protocol JIABAILE
2025-01-28 New H36 protocol - 1 ID
2025-01-29 JIABAILE RX ID in EEPROM
    Not an autobind protocol anymore.
2025-01-29 Fix DSMR
2025-01-30 Improve DSM telemetry stability?
2025-01-30 Hontai/XKK170 new subprotocol
2025-02-06 New JIABAILE/Gyro subprotocol
2025-02-06 Yuxiang multi IDs/Freqs
2025-02-09 New XK2/P10 sub protocol
2025-02-18 UDIRC new protocol / WIP
2025-02-19 XN297Emu add ReSendPayload
2025-02-21 KAMTOM new surface protocol
    Missing low batt telem
2025-02-22 Update Compiling.md (#1078)
2025-02-22 KAMTOM telemetry
2025-02-24 SHENQI2 new protocol
2025-02-25 SLT2 trial
2025-02-25 SLT2 trial 2
2025-02-25 SLT2 trial 3
2025-02-25 SLT2 last trial?
2025-02-26 SLT2 final
2025-02-26 DSMR SR6200 test 1
2025-02-27 ASF try 1
2025-03-10 New SFC protocol WL91x
2025-03-12 Add FX_QF012 subprotocol (#1091)
2025-03-12 FX/QF012 details
2025-03-12 FX/QF012 details 2
2025-03-12 XK2 Gyro off
2025-03-12 MT99xx Trim channels
2025-03-13 MouldKg multi 6 ports brick support
2025-03-13 MouldKg renamed subprotocols
2025-03-13 FX small changes
2025-03-13 FX telemetry
2025-03-14 MouldKg swap CH5 and CH6
2025-03-20 Added AFHDS2A BS4/BS6 support
2025-03-20 MouldKg update
2025-03-21 FX/QF012 telemetry
2025-03-28 XK2 low batt telemetry
2025-04-02 SGF22 telemetry
2025-04-02 DSMR timing
2025-04-03 Update Protocols_Details.md (#1101)
2025-04-16 SGF22 telem improvement?
2025-05-09 Enable Telemetry on DumbRC receivers
    Tested with X6FGv1.1, X6FP, X6DC(G)v1.1
    I also tested with multiple X6F receivers and some gave RSSI Telem and some gave nothing.
    2 of them had the same PCB as the X6FP and neither gave telemetry.
    I had a third with the same PCB with the X6FP which did give RSSI
    and of my two with an older PCB one gives RSSI telem and the other does not.
    Of the receivers I tried only one set packet_in[6] to match the TX packet[1] and it was the
2025-05-10 Enable Telemetry on DumbRC receivers (#1111)
    Tested with X6FGv1.1, X6FP, X6DC(G)v1.1
    I also tested with multiple X6F receivers and some gave RSSI Telem and some gave nothing.
    2 of them had the same PCB as the X6FP and neither gave telemetry.
    I had a third with the same PCB with the X6FP which did give RSSI
    and of my two with an older PCB one gives RSSI telem and the other does not.
    Of the receivers I tried only one set packet_in[6] to match the TX packet[1] and it was the
2025-07-26 preliminary support for new CX-10
2025-07-27 WPL new protocol
    Only 1 ID
2025-07-27 MT99xx/SU35: removed autobind
2025-07-27 WPL try 2
2025-07-27 use preproc if instead of lang if, use id bytes 2 and 3 instead of 0 and 1, formatting
2025-07-27 preliminary impl of CX-10 proto as sub of SGF22
2025-07-27 WPL 3rd try
2025-07-27 WPL 4th
2025-07-27 WPL 5
2025-07-27 WPL 1 ID
2025-07-28 SGF22/CX10 new subprotocol
    Only 2 IDs
2025-08-25 Wrong ID used for FX (58 instead of 28)
2025-09-16 Fix for no bind on SG F22 variants
2025-12-11 Update XK2_ccnrf.ino
    add stunt flag for SkyViper Vector.
2026-02-14 Update FX_nrf24l01.ino
    add FX_BM26 subprotocol
2026-02-14 Update _Config.h
    add FX_BM26 subprotocol
2026-02-14 Update Multi.txt
    add FX_BM26 subprotocol
2026-02-14 Update Multi_Protos.ino
    add FX_BM26 subprotocol
2026-02-14 Update Protocols_Details.md
    add FX_BM26 subprotocol and "Stunt" in XK2 for SkyViper Vector
2026-05-09 (fix) Remove NCC1701 for space needed to upload correctly to flash
    Although the MULTI_AIR builds are completing successfully for the 128Kb versions, just under the 120808 byte threshold, these builds do not work properly when uploaded to MPM. As different builds nea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
2026-05-09 Add post-build size check for 128KB builds
    Agent-Logs-Url: https://github.com/MRC3742/DIY-Multiprotocol-TX-Module/sessions/866c69d6-fc73-4d47-b3ca-2b36e2f29ec9
2026-05-25 Add T-Smart - Model XBM-37 Protocol Support (#22)
    * Apply XBM-37 protocol changes excluding capture files
    Agent-Logs-Url: https://github.com/MRC3742/DIY-Multiprotocol-TX-Module/sessions/f5cfeacc-2389-482f-bb92-824afdf1639c
2026-06-30 Update Hontai_nrf24l01.ino
    add support of optical flow sensor
2026-06-30 Update Protocols_Details.md
    add support for XK K270 optical flow sensor

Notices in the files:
parts and their libraries:
SparkFun-FreqCtrl: Licensing: CC v3.0 Share-Alike You are welcome to use this library for commercial purposes.
SparkFun-PowerIC: Licensing: Creative Commons ShareAlike 4.0 International - https://creativecommons.org/licenses/by-sa/4.0
con-molex-kk: Copyright (C) 2010, Bob Starr
